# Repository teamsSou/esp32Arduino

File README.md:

# esp32Arduino
Espc06's Arduino Projects

■Wifi　Connetサンプル

■ESP32をWebAPIサーバ・Webサーバにするサンプル
https://qiita.com/poruruba/items/0e539875ecfbdbfb23db

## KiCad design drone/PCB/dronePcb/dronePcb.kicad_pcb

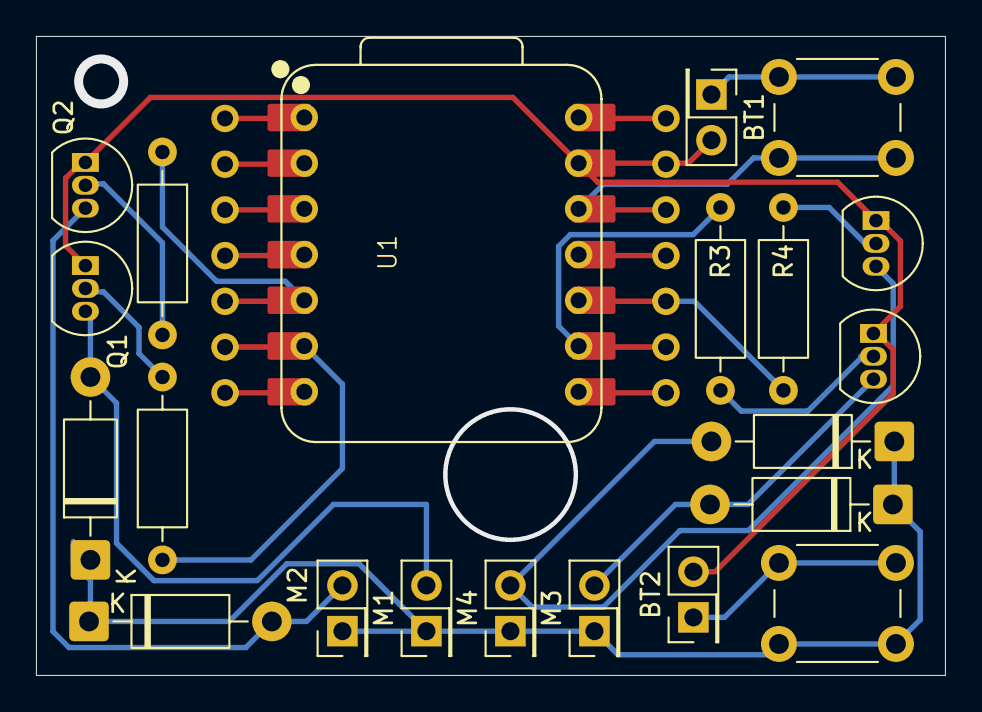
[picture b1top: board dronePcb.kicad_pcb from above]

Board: 2 copper layers, 50.5 x 35.5 mm, 21 parts (0 on the bottom side), 17 nets.

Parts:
BT1, BT2: 3.3v; PinHeader_2x01_P2.54mm_Vertical
D1, D2, D3, D4: 1N4007; D_DO-41_SOD81_P10.16mm_Horizontal
M1, M3, M4: Motor_DC; PinHeader_2x01_P2.54mm_Vertical
M2: PinHeader_2x01_P2.54mm_Vertical
Q1, Q2, Q3, Q4: PN2222A; TO-92_Inline
R1, R2, R3, R4: 220Ω; R_Axial_DIN0207_L6.3mm_D2.5mm_P10.16mm_Horizontal
SW1, SW2: SW_Push; SW_PUSH_6mm
U1: XIAO-ESP32-C6-DIP

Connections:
GNDREF: BT1.2 (-), BT2.2 (-), Q1.1 (E), Q2.1 (E), Q3.1 (E), Q4.1 (E), U1.13 (GND)
unnamed: BT1.1 (+), SW1.2
unnamed: BT2.1 (+), SW2.2
unnamed: D1.2 (A), M1.2 (-), Q1.3 (C)
unnamed: D1.1 (K), D2.1 (K), D3.1 (K), D4.1 (K), M1.1 (+), M2.1 (+), M3.1 (+), M4.1 (+), SW2.1
unnamed: D2.2 (A), M2.2 (-), Q2.3 (C)
unnamed: D3.2 (A), M3.2 (-), Q3.3 (C)
unnamed: D4.2 (A), M4.2 (-), Q4.3 (C)
unnamed: Q1.2 (B), R1.2
unnamed: Q2.2 (B), R2.2
unnamed: Q3.2 (B), R3.2
unnamed: Q4.2 (B), R4.2
unnamed: SW1.1, U1.12 (3V3)
unnamed: R3.1, U1.9 (GPIO19_D8_SCK)
unnamed: R4.1, U1.10 (GPIO20_D9_MISO)
unnamed: R2.1, U1.5 (GPIO22_D4_SDA)
unnamed: R1.1, U1.6 (GPIO23_D5_SCL)

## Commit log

2026-03-15 Update README with new sample project links
    Added sample projects for WiFi connection and ESP32 as a WebAPI/Web server.
2026-03-17 Create webserver_4motors.ino
    フォルダー調整
2026-03-17 フォルダー調整
2026-03-18 Memo Added
2026-03-19 CHANGE PORT
2026-03-24 pcb作成
2026-03-26 WiFiAPモードを追加
    動作未確認
2026-03-27 modify ecr error
2026-03-29 エラー解消
2026-04-07 PCB作成エラーなし
2026-04-07 close kikad
